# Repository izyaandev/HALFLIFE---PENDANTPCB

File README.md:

# Half Life Pendant

A small wearable that listens for conversations, records them **only when someone is actually talking**, stores them,
and uses AI to turn them into searchable summaries, so you never lose the thing someone said three weeks ago.

I'm Izyaan and this is my [Hack Club Half Life](https://halflife.hackclub.com) project. A recorder you wear is only okay
if the people around you can trust it, so the whole design starts from one rule: **privacy comes first, and it has to be physical**.

> **Status: design phase.** Everything in this repo is designed and checked in software (PCB design checks, 3D fit check,
> unit tests). Nothing has been manufactured or flashed yet. Each section says exactly what has and hasn't been verified.

## What makes it different

- **A real hardware privacy switch.** The slide switch sits in series with the microphone's power. Switch off and the mic has *no power at all*, so no firmware bug can make it listen. A pin on the microcontroller reads the mic rail, so the firmware always knows the switch state.
- **A recording light you can see.** The red LED is on only while audio is being recorded, and a printed light pipe carries it up to the lid.
- **It never records silence.** A voice detector with an adaptive noise floor wakes the recorder only when someone is talking, which saves battery and storage.
- **It never cuts off the first word.** It keeps 1.5 s of audio from *before* speech was detected and writes it into the file.
- **Bookmarks.** One button press marks "this part matters" inside the current recording.
- **Nothing is lost offline.** Audio goes to a microSD card first, uploads when Wi-Fi is available, and is deleted from the card only after the server confirms.
- **An AI router.** Easy jobs (tags, titles, short summaries) go to a cheap fast model; long conversations go to a stronger one, with fallback if a provider is down.

## How it works

```mermaid
flowchart LR
  SW[privacy slide switch] -- cuts power --> MIC[INMP441 mic]
  MIC --> ESP[XIAO ESP32-S3]
  ESP --> VAD{someone talking?}
  VAD -- yes, plus 1.5 s pre-roll --> SD[(microSD, WAV chunks)]
  SD -- Wi-Fi --> API[backend API]
  API --> STT[speech to text]
  STT --> R[AI router]
  R --> LLM[summary, action items, tags]
  LLM --> DB[(database + vector search)]
```

## Hardware

### Carrier PCB

A 28 x 50 mm two-layer board. The XIAO ESP32-S3 Sense plugs into two 7-pin sockets, and the board adds everything the pendant needs around it.

| XIAO pin | GPIO | Job |
|---|---|---|
| D0 | 1 | I2S bit clock to the mic |
| D1 | 2 | I2S word select to the mic |
| D2 | 3 | I2S data from the mic |
| D3 | 4 | battery voltage (2 x 200k divider) |
| D4 | 5 | bookmark button |
| D5 | 6 | reads the mic power rail (privacy switch state) |
| D6 | 43 | red recording LED |

Design details I care about:
- a **100k pulldown** on the mic rail so pin D5 reads a clean LOW when the switch is off (otherwise it would float)
- 100 nF + 10 uF decoupling on the mic supply
- all small passives are 0603 or bigger so the board is hand-solderable
- traces 0.2 mm, vias 0.3 mm hole / 0.6 mm pad, standard 2-layer fab rules

**Files:** KiCad project (`hardware/pcb/half-life-pendant.kicad_*`), schematic PDF, Gerbers + drill (`hardware/pcb/gerbers/`),
pick-and-place, and the [tscircuit](https://tscircuit.com) source the board was generated from. The design passes
tscircuit's netlist, schematic-placement, PCB-placement, build and short-circuit checks.

**Not verified yet:** the PCB has not been opened in KiCad's own DRC or built into a physical board, and the XIAO socket spacing,
switch, button and JST footprints are generic. See [docs/ORDERING.md](docs/ORDERING.md) for the checklist before ordering.

### 3D-printed enclosure

Five parts designed in CadQuery (STEP + STL in `hardware/3d/`): base, lid, button plunger, slider cap and LED light pipe.

- the battery sits in a bay *under* the PCB, the XIAO stack on top, with a USB-C opening in the lid end wall
- the privacy slider and bookmark button are small printed parts that reach down to the real switch and button
- base and lid join with a tongue-and-groove lip, and a lanyard ear sits at the bottom end
- I modelled every real component (PCB, headers, XIAO stack, battery, mic module, switch, button, LED, connector) and **checked every pair for overlap: no printed part collides with anything**

It is chunky (33.4 x 64.9 x 30.8 mm). The mic breakout stands 14 mm tall, which is why the lid has a ridge over it, and the 8.5 mm sockets add height.
v0.2 can fix that with low-profile sockets or by soldering the XIAO straight to the board.

### Bill of materials

Full list in [`bom.csv`](bom.csv): carrier-board parts, plug-in modules (XIAO, INMP441), battery, microSD and the printed parts.

## Firmware

PlatformIO / Arduino project in `firmware/`: voice detection, pre-roll buffer, WAV chunks on the microSD, bookmarks, upload task, battery monitoring and privacy-switch handling.

The voice detector is covered by 10 unit tests that run on a normal PC (no board needed), and they caught a real bug while I was writing it:
in a noisy room the background noise counted as speech, so the detector never adapted to the room. Fixed with a noise floor that drops instantly and rises slowly, plus calibration at boot.

The rest of the firmware is written against the real pin map but **has not been compiled for the ESP32 or run on hardware**. See [firmware/README.md](firmware/README.md).

## Backend

A small FastAPI server (`backend/`) that matches what the firmware uploads, with the AI router, a mock pipeline and the planned database schema. 7 tests pass. Transcription and model calls are stubs until I pick providers.

```mermaid
erDiagram
  DEVICES ||--o{ RECORDINGS : captures
  RECORDINGS ||--o{ BOOKMARKS : has
  DEVICES { uuid id PK
            string name
            timestamp last_seen }
  RECORDINGS { uuid id PK
               uuid device_id FK
               timestamp created_at
               real duration_s
               text transcript
               text summary
               json action_items
               string model_used
               vector embedding }
  BOOKMARKS { uuid id PK
              uuid recording_id FK
              real at_second }
```

## Try it without hardware

Open `simulator/index.html` in a browser. It is an interactive model of the pendant's logic: flip the privacy switch, hold the speak button, watch the voice detector with pre-roll and hangover, see recordings queue on the SD card and upload when you switch Wi-Fi on, and watch the battery drain. The numbers in it are design assumptions, not measurements.

## Repo map

| path | what's in it |
|---|---|
| `hardware/pcb/` | KiCad project, schematic PDF, Gerbers, pick-and-place, tscircuit source |
| `hardware/3d/` | CadQuery model, STEP + STL files, render script |
| `bom.csv` | bill of materials |
| `firmware/` | ESP32-S3 firmware + voice detector tests |
| `backend/` | mock server, AI router, schema, tests |
| `simulator/` | interactive browser simulator |
| `docs/` | design notes, ordering guide, images |

## What's next

1. Check footprints against the real parts and order a small batch of boards
2. Compile and flash the firmware, tune the voice detector on real audio
3. Print the case, check the fit, then slim it down for v0.2
4. Pick real transcription and model providers, build the companion app, add encryption and auto-delete

## Credits

Built for Hack Club Half Life. PCB generated with tscircuit, 3D parts with CadQuery.

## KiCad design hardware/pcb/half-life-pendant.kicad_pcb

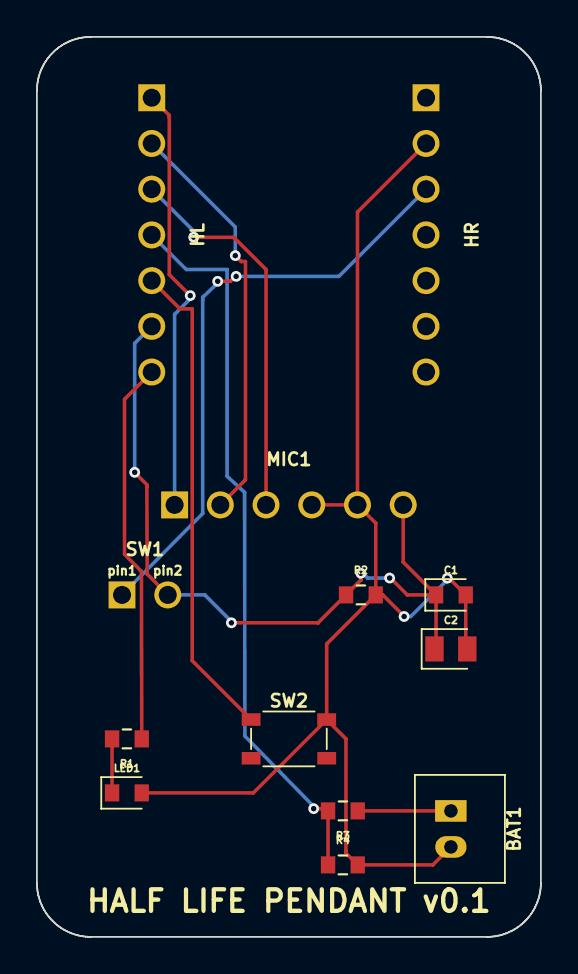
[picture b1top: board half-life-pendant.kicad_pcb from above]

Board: 2 copper layers, 28.0 x 50.0 mm, 13 parts (0 on the bottom side), 11 nets.

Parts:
BAT1: BAT1; power_source_jst2_p2mm_ph
C1: 100nF; capacitor_cap0603
C2: 10uF; capacitor_cap0805
HL: HL; pin_header_pinrow7_p2_54_nopinlabels_female
HR: HR; pin_header_pinrow7_p2_54_nopinlabels_female
LED1: LED; led_0603_color_red
MIC1: MIC1; pin_header_pinrow6_p2_54_nopinlabels_female
R1: 220Ω; resistor_res0603
R2: 100kΩ; resistor_res0603
R3, R4: 200kΩ; resistor_res0603
SW1: SW; switch_pinrow2_p2_54mm
SW2: SW2; push_button_smdpushbutton

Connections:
GND: BAT1.2, C1.2, C2.2, HR.2, LED1.2, MIC1.4, MIC1.5, R2.2, R4.2, SW2.2
HL.D4 to SW2.pin1: HL.5, SW2.1
HL.D6 to R1.pin1: HL.7, R1.1
MIC1.SCK to HL.D0: HL.1, MIC1.1
MIC1.SD to HL.D2: HL.3, MIC1.3
MIC1.WS to HL.D1: HL.2, MIC1.2
MIC_VDD: C1.1, C2.1, HL.6, MIC1.6, R2.1, SW1.2
R1.pin2 to LED1.pos: LED1.1, R1.2
SW1.pin1 to HR.V3V3: HR.3, SW1.1
VBAT: BAT1.1, R3.1
VBAT_SENSE: HL.4, R3.2, R4.1
